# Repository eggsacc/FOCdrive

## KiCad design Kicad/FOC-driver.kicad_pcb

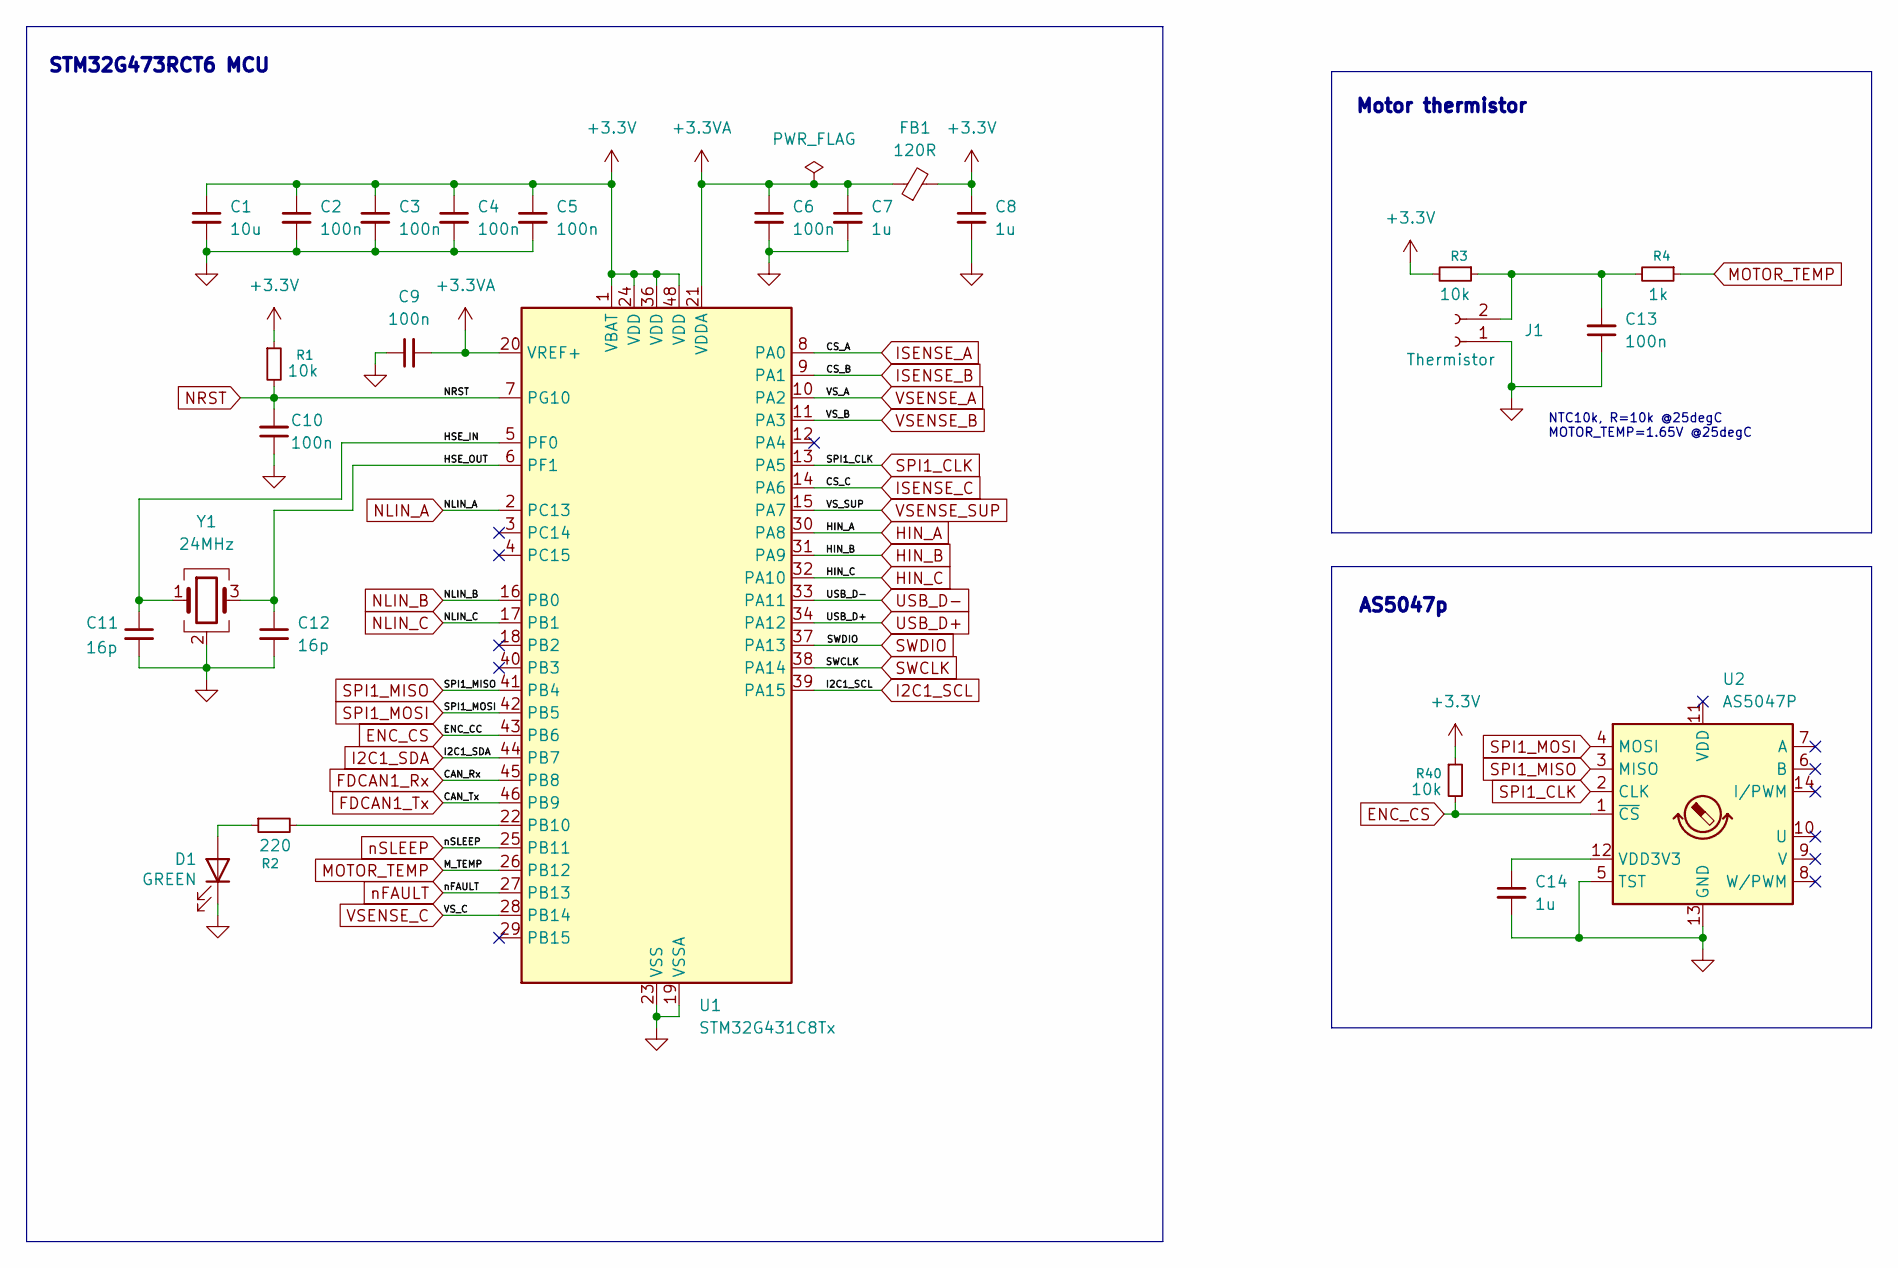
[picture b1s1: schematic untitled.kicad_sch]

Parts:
C1: 10u; C_1206_3216Metric
C2, C3, C4, C5, C6, C9, C13: 100n; C_0402_1005Metric
C7, C8, C14: 1u; C_0603_1608Metric
C10: 100n; C_01005_0402Metric
C11, C12: 16p; C_0402_1005Metric
D1: GREEN; LED_0603_1608Metric
FB1: 120R; L_0603_1608Metric
J1: Thermistor; 2p SolderWire Pad
R1, R3, R40: 10k; R_0402_1005Metric
R2: 220; R_0603_1608Metric
R4: 1k; R_0402_1005Metric
U1: STM32G431C8Tx; LQFP-48_7x7mm_P0.5mm
U2: AS5047P; TSSOP-14_4.4x5mm_P0.65mm
Y1: 24MHz; Crystal_SMD_3225-4Pin_3.2x2.5mm

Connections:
+3.3V: C1.1, C2.1, C3.1, C4.1, C5.1, C8.1, FB1.2, R1.1, R3.2, R40.1, U1.1 (VBAT), U1.24 (VDD), U1.36 (VDD), U1.48 (VDD); also elsewhere on the board
+3.3VA: C6.1, C7.1, C9.2, FB1.1, U1.20 (VREF+), U1.21 (VDDA); also elsewhere on the board
/mcu/HSE_IN: C11.1, U1.5 (PF0), Y1.1
/mcu/HSE_OUT: C12.1, U1.6 (PF1), Y1.3
ENC_CS: R40.2, U1.43 (PB6), U2.1 (~CS)
FDCAN1_Rx: U1.45 (PB8); also elsewhere on the board
FDCAN1_Tx: U1.46 (PB9); also elsewhere on the board
HIN_A: U1.30 (PA8); also elsewhere on the board
HIN_B: U1.31 (PA9); also elsewhere on the board
HIN_C: U1.32 (PA10); also elsewhere on the board
I2C1_SCL: U1.39 (PA15); also elsewhere on the board
I2C1_SDA: U1.44 (PB7); also elsewhere on the board
ISENSE_A: U1.8 (PA0); also elsewhere on the board
ISENSE_B: U1.9 (PA1); also elsewhere on the board
ISENSE_C: U1.14 (PA6); also elsewhere on the board
LSS: C1.2, C2.2, C3.2, C4.2, C5.2, C6.2, C7.2, C8.2, C9.1, C10.1, C11.2, C12.2, C13.1, C14.2, D1.1 (K), J1.1, U1.19 (VSSA), U1.23 (VSS), U1.35 (VSS), U1.47 (VSS), U2.5 (TST), U2.13 (GND), Y1.2 (G), Y1.4 (G); also elsewhere on the board
MOTOR_TEMP: R4.1, U1.26 (PB12)
NLIN_A: U1.2 (PC13); also elsewhere on the board
NLIN_B: U1.16 (PB0); also elsewhere on the board
NLIN_C: U1.17 (PB1); also elsewhere on the board
NRST: C10.2, R1.2, U1.7 (PG10); also elsewhere on the board
unnamed: D1.2 (A), R2.1
unnamed: C13.2, J1.2, R3.1, R4.2
unnamed: R2.2, U1.22 (PB10)
unnamed: C14.1, U2.12 (VDD3V3)
SPI1_CLK: U1.13 (PA5), U2.2 (CLK)
SPI1_MISO: U1.41 (PB4), U2.3 (MISO)
SPI1_MOSI: U1.42 (PB5), U2.4 (MOSI)
SWCLK: U1.38 (PA14); also elsewhere on the board
SWDIO: U1.37 (PA13); also elsewhere on the board
USB_D+: U1.34 (PA12); also elsewhere on the board
USB_D-: U1.33 (PA11); also elsewhere on the board
VSENSE_A: U1.10 (PA2); also elsewhere on the board
VSENSE_B: U1.11 (PA3); also elsewhere on the board
VSENSE_C: U1.28 (PB14); also elsewhere on the board
VSENSE_SUP: U1.15 (PA7); also elsewhere on the board
nFAULT: U1.27 (PB13); also elsewhere on the board
nSLEEP: U1.25 (PB11); also elsewhere on the board

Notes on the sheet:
AS5047p
STM32G473RCT6 MCU
NTC10k, R=10k @25degC MOTOR_TEMP=1.65V @25degC
Motor thermistor

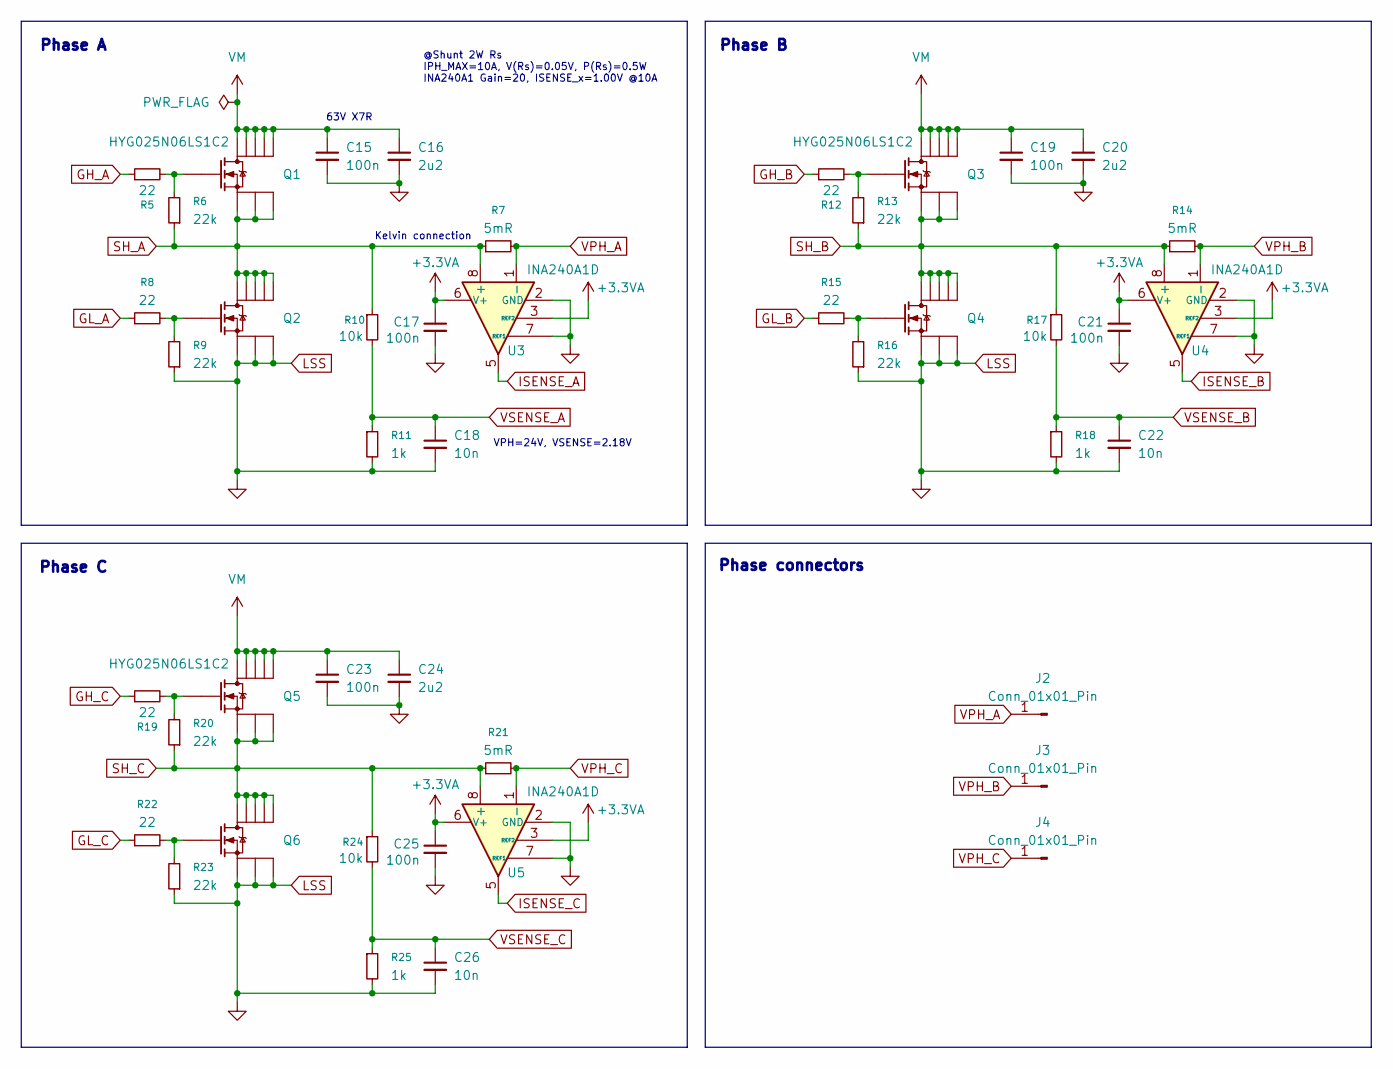
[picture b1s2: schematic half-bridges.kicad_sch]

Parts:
C15, C17, C19, C21, C23, C25: 100n; C_0603_1608Metric
C16, C20, C24: 2u2; C_1206_3216Metric
C18, C22, C26: 10n; C_0402_1005Metric
J2, J3, J4: Conn_01x01_Pin; WireSolder-ID1.6mm-OD3mm
Q1, Q2, Q3, Q4, Q5, Q6: HYG025N06LS1C2
R5, R8, R12, R15, R19, R22: 22; R_0603_1608Metric
R6, R9, R13, R16, R20, R23: 22k; R_0603_1608Metric
R7, R14, R21: 5mR; R_2512_6332Metric
R10, R17, R24: 10k; R_0402_1005Metric
R11, R18, R25: 1k; R_0402_1005Metric
U3, U4, U5: INA240A1D; SOIC-8_3.9x4.9mm_P1.27mm

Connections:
+3.3VA: C17.1, C21.1, C25.1, U3.3 (REF2), U3.6 (V+), U4.3 (REF2), U4.6 (V+), U5.3 (REF2), U5.6 (V+); also elsewhere on the board
GH_A: R5.1; also elsewhere on the board
GH_B: R12.1; also elsewhere on the board
GH_C: R19.1; also elsewhere on the board
GL_A: R8.1; also elsewhere on the board
GL_B: R15.1; also elsewhere on the board
GL_C: R22.1; also elsewhere on the board
ISENSE_A: U3.5; also elsewhere on the board
ISENSE_B: U4.5; also elsewhere on the board
ISENSE_C: U5.5; also elsewhere on the board
LSS: C15.2, C16.2, C17.2, C18.2, C19.2, C20.2, C21.2, C22.2, C23.2, C24.2, C25.2, C26.2, Q2.1 (S), Q2.2 (S), Q2.3 (S), Q4.1 (S), Q4.2 (S), Q4.3 (S), Q6.1 (S), Q6.2 (S), Q6.3 (S), R9.1, R11.2, R16.1, R18.2, R23.1, R25.2, U3.2 (GND), U3.4 (GND), U3.7 (REF1), U4.2 (GND), U4.4 (GND), U4.7 (REF1), U5.2 (GND), U5.4 (GND), U5.7 (REF1); also elsewhere on the board
unnamed: Q1.4 (G), R5.2, R6.2
unnamed: Q2.4 (G), R8.2, R9.2
unnamed: Q3.4 (G), R12.2, R13.2
unnamed: Q4.4 (G), R15.2, R16.2
unnamed: Q5.4 (G), R19.2, R20.2
unnamed: Q6.4 (G), R22.2, R23.2
PVDD: C15.1, C16.1, C19.1, C20.1, C23.1, C24.1, Q1.5 (D), Q1.6, Q1.7, Q1.8, Q1.9, Q3.5 (D), Q3.6, Q3.7, Q3.8, Q3.9, Q5.5 (D), Q5.6, Q5.7, Q5.8, Q5.9; also elsewhere on the board
SH_A: Q1.1 (S), Q1.2 (S), Q1.3 (S), Q2.5 (D), Q2.6, Q2.7, Q2.8, Q2.9, R6.1, R7.1, R10.1, U3.8 (+); also elsewhere on the board
SH_B: Q3.1 (S), Q3.2 (S), Q3.3 (S), Q4.5 (D), Q4.6, Q4.7, Q4.8, Q4.9, R13.1, R14.1, R17.1, U4.8 (+); also elsewhere on the board
SH_C: Q5.1 (S), Q5.2 (S), Q5.3 (S), Q6.5 (D), Q6.6, Q6.7, Q6.8, Q6.9, R20.1, R21.1, R24.1, U5.8 (+); also elsewhere on the board
VPH_A: J2.1 (Pin_1_1), R7.2, U3.1 (-)
VPH_B: J3.1 (Pin_1_1), R14.2, U4.1 (-)
VPH_C: J4.1 (Pin_1_1), R21.2, U5.1 (-)
VSENSE_A: C18.1, R10.2, R11.1; also elsewhere on the board
VSENSE_B: C22.1, R17.2, R18.1; also elsewhere on the board
VSENSE_C: C26.1, R24.2, R25.1; also elsewhere on the board

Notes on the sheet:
Phase A
VPH=24V, VSENSE=2.18V
@Shunt 2W Rs IPH_MAX=10A, V(Rs)=0.05V, P(Rs)=0.5W INA240A1 Gain=20, ISENSE_x=1.00V @10A
Phase B
63V X7R
Phase connectors
Phase C
Kelvin connection

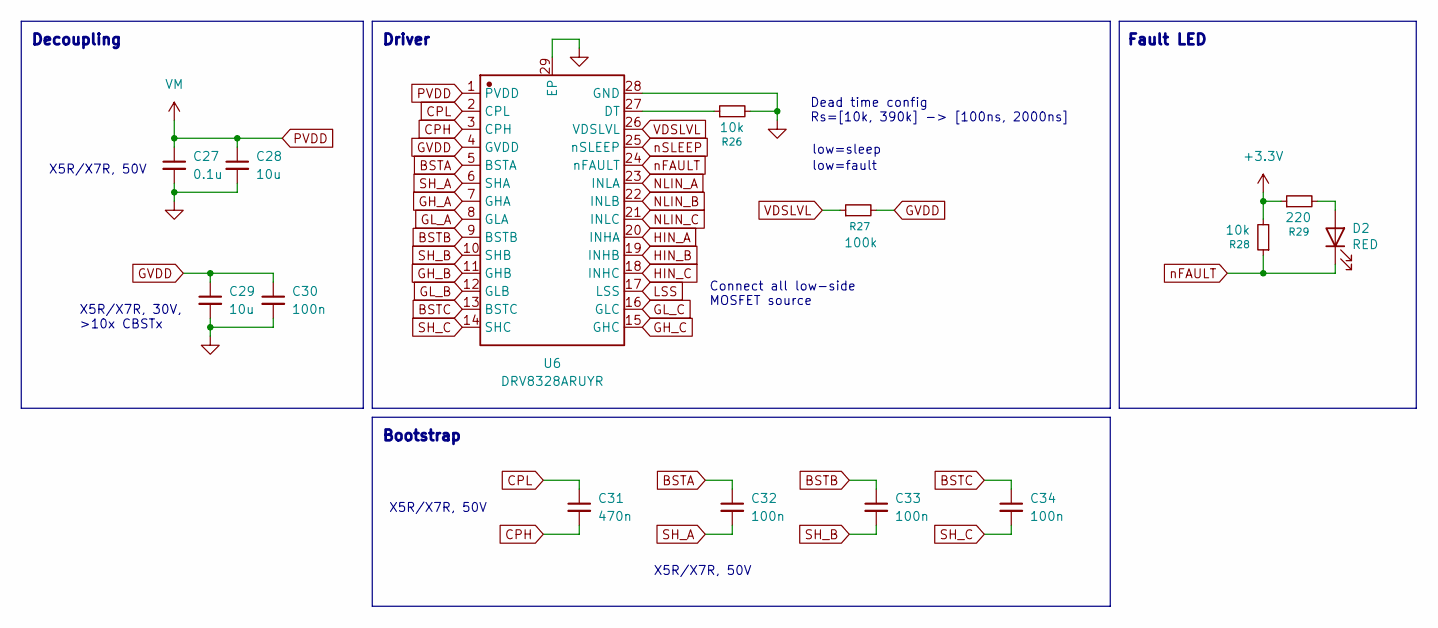
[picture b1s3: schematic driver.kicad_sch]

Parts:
C27: 0.1u; C_0603_1608Metric
C28, C29: 10u; C_1206_3216Metric
C30: 100n; C_0402_1005Metric
C31: 470n; C_0805_2012Metric
C32, C33, C34: 100n; C_0805_2012Metric
D2: RED; LED_0603_1608Metric
R26, R28: 10k; R_0402_1005Metric
R27: 100k; R_0402_1005Metric
R29: 220; R_0603_1608Metric
U6: DRV8328ARUYR; QFN-28_L4.0-W4.0-P0.40-BL-EP2.6 DRV8328; Manufacturer Part DRV8328BRUYR

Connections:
+3.3V: R28.2, R29.1; also elsewhere on the board
BSTA: C32.1, U6.5 (BSTA)
BSTB: C33.1, U6.9 (BSTB)
BSTC: C34.1, U6.13 (BSTC)
CPH: C31.2, U6.3 (CPH)
CPL: C31.1, U6.2 (CPL)
GH_A: U6.7 (GHA); also elsewhere on the board
GH_B: U6.11 (GHB); also elsewhere on the board
GH_C: U6.15 (GHC); also elsewhere on the board
GL_A: U6.8 (GLA); also elsewhere on the board
GL_B: U6.12 (GLB); also elsewhere on the board
GL_C: U6.16 (GLC); also elsewhere on the board
GVDD: C29.1, C30.1, R27.2, U6.4 (GVDD)
HIN_A: U6.20 (INHA); also elsewhere on the board
HIN_B: U6.19 (INHB); also elsewhere on the board
HIN_C: U6.18 (INHC); also elsewhere on the board
LSS: C27.2, C28.2, C29.2, C30.2, R26.2, U6.17 (LSS), U6.28 (GND), U6.29 (EP); also elsewhere on the board
NLIN_A: U6.23 (INLA); also elsewhere on the board
NLIN_B: U6.22 (INLB); also elsewhere on the board
NLIN_C: U6.21 (INLC); also elsewhere on the board
unnamed: D2.2 (A), R29.2
unnamed: R26.1, U6.27 (DT)
PVDD: C27.1, C28.1, U6.1 (PVDD); also elsewhere on the board
SH_A: C32.2, U6.6 (SHA); also elsewhere on the board
SH_B: C33.2, U6.10 (SHB); also elsewhere on the board
SH_C: C34.2, U6.14 (SHC); also elsewhere on the board
VDSLVL: R27.1, U6.26 (VDSLVL)
nFAULT: D2.1 (K), R28.1, U6.24 (nFAULT); also elsewhere on the board
nSLEEP: U6.25 (nSLEEP); also elsewhere on the board

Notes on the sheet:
Bootstrap
Fault LED
Connect all low-side MOSFET source
Driver
X5R/X7R, 50V
Decoupling
low=sleep
low=fault
X5R/X7R, 30V, >10x CBSTx
Dead time config Rs=[10k, 390k] -> [100ns, 2000ns]

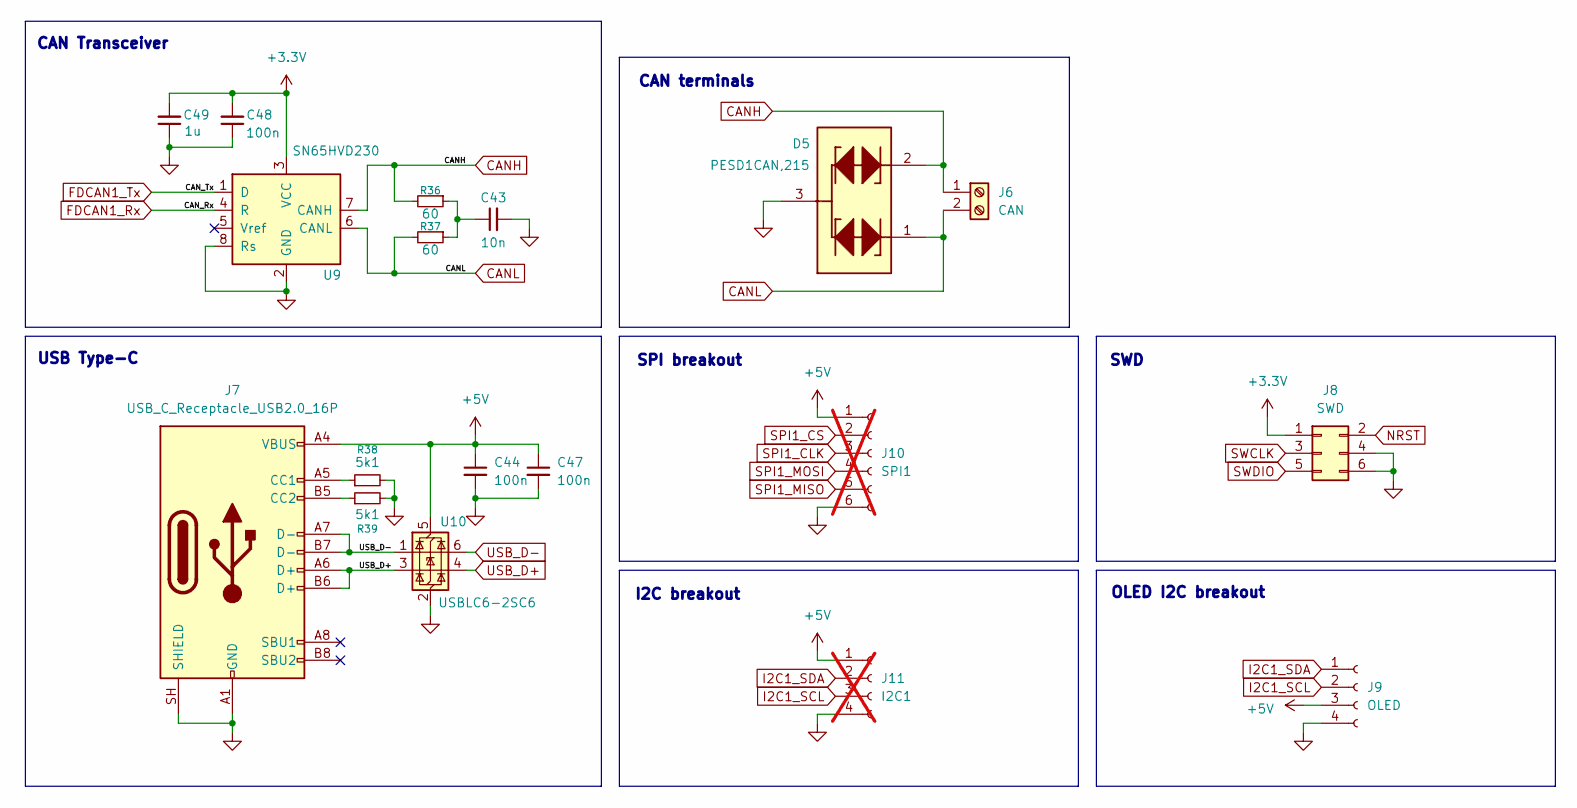
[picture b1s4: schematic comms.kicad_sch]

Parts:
C43: 10n; C_0402_1005Metric
C44, C47, C48: 100n; C_0402_1005Metric
C49: 1u; C_0402_1005Metric
D5: PESD1CAN,215; PESD1CAN; Manufacturer Part PESD1CAN,215
J6: CAN; TerminalBlock_Xinya_XY308-2.54-2P_1x02_P2.54mm_Horizontal
J7: USB_C_Receptacle_USB2.0_16P; USB_C_Receptacle_GCT_USB4105-xx-A_16P_TopMnt_Horizontal
J8: SWD; PinSocket_2x03_P1.27mm_Vertical
J9: OLED; PinSocket_1x04_P2.54mm_Vertical
J10: SPI1; JST_ZE_S06B-ZESK-2D_1x06_P1.50mm_Horizontal; not fitted
J11: I2C1; JST_ZE_S04B-ZESK-2D_1x04_P1.50mm_Horizontal; not fitted
R36, R37: 60; R_0603_1608Metric
R38, R39: 5k1; R_0402_1005Metric
U9: SN65HVD230; SOIC-8_3.9x4.9mm_P1.27mm
U10: USBLC6-2SC6; SOT-23-6

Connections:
+3.3V: C48.2, C49.2, J8.1, U9.3 (VCC); also elsewhere on the board
+5V: C44.1, C47.1, J7.A4 (VBUS), J7.A9 (VBUS), J7.B4 (VBUS), J7.B9 (VBUS), J9.3, J10.1, J11.1, U10.5 (VBUS); also elsewhere on the board
CANH: D5.2, J6.1, R36.2, U9.7 (CANH)
CANL: D5.1, J6.2, R37.2, U9.6 (CANL)
FDCAN1_Rx: U9.4 (R); also elsewhere on the board
FDCAN1_Tx: U9.1 (D); also elsewhere on the board
I2C1_SCL: J9.2, J11.3; also elsewhere on the board
I2C1_SDA: J9.1, J11.2; also elsewhere on the board
LSS: C43.2, C44.2, C47.2, C48.1, C49.1, D5.3, J7.A1 (GND), J7.A12 (GND), J7.B1 (GND), J7.B12 (GND), J7.SH (SHIELD), J8.4, J8.6, J9.4, J10.6, J11.4, R38.2, R39.2, U9.2 (GND), U9.8 (Rs), U10.2 (GND); also elsewhere on the board
NRST: J8.2; also elsewhere on the board
unnamed: C43.1, R36.1, R37.1
unnamed: J7.A5 (CC1), R38.1
unnamed: J7.B5 (CC2), R39.1
SWCLK: J8.3; also elsewhere on the board
SWDIO: J8.5; also elsewhere on the board
USB_D+: J7.A6 (D+), J7.B6 (D+), U10.3 (I/O2), U10.4 (I/O2); also elsewhere on the board
USB_D-: J7.A7 (D-), J7.B7 (D-), U10.1 (I/O1), U10.6 (I/O1); also elsewhere on the board

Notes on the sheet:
OLED I2C breakout
SWD
CAN Transceiver
USB Type-C
SPI breakout
I2C breakout
CAN terminals

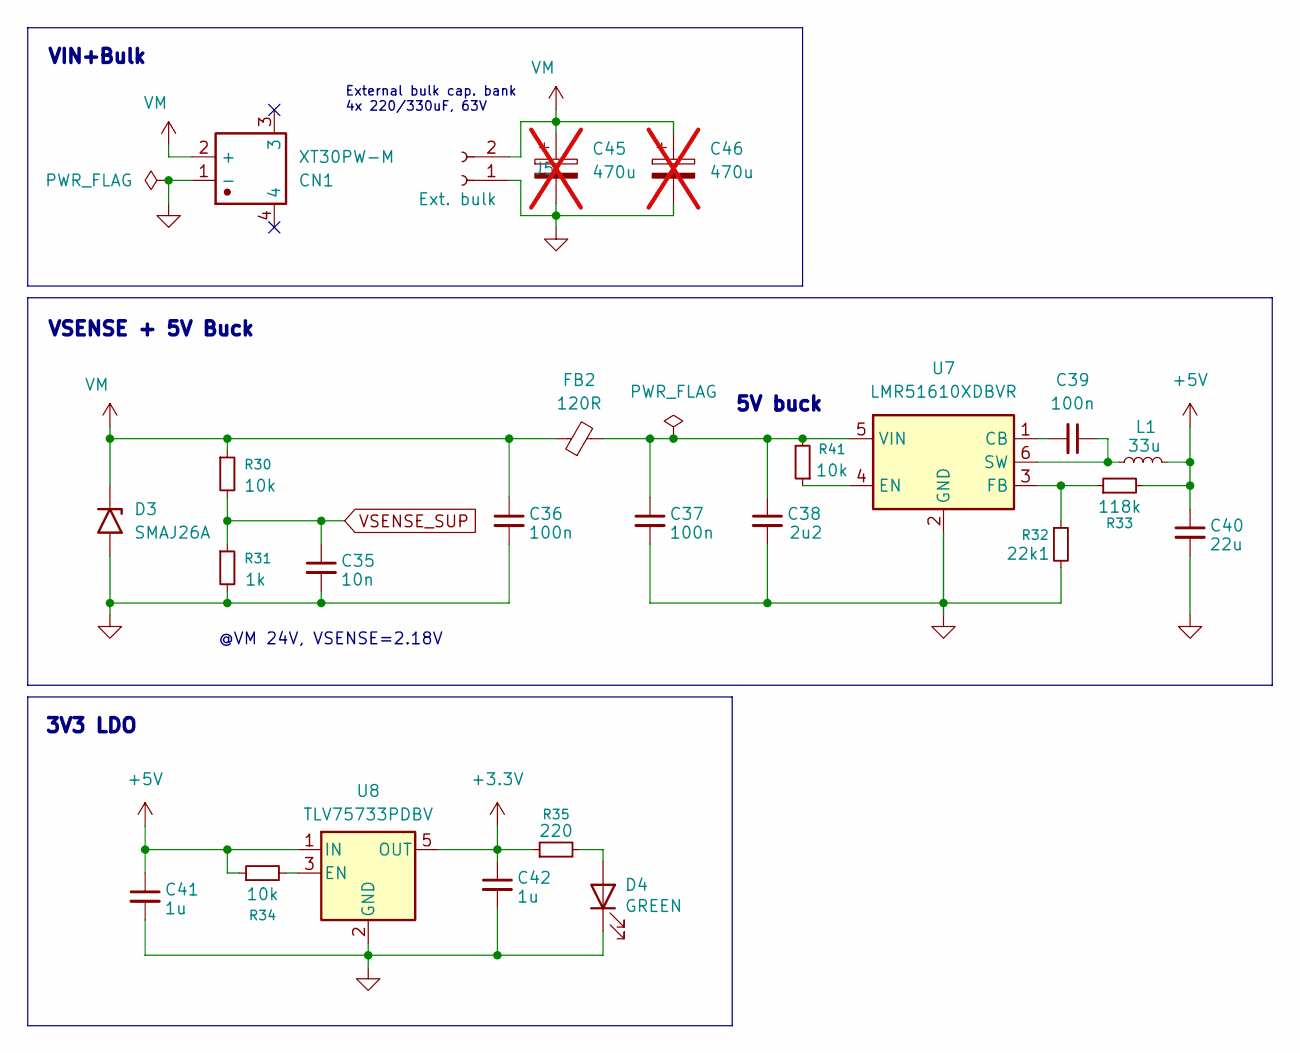
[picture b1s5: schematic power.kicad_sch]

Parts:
C35: 10n; C_0402_1005Metric
C36, C37, C39: 100n; C_0402_1005Metric
C38: 2u2; C_0805_2012Metric
C40: 22u; C_1206_3216Metric
C41, C42: 1u; C_0603_1608Metric
C45, C46: 470u; CP_Elec_10x12.5; not fitted
CN1: XT30PW-M; CONN-TH_XT30PW-M; Manufacturer Part XT60PW-M
D3: SMAJ26A; D_SMA
D4: GREEN; LED_0603_1608Metric
FB2: 120R; L_0603_1608Metric
J5: Ext. bulk; 2p WireSolder 1.3mmID_2mmOD
L1: 33u; L_10.4x10.4_H4.8
R30, R34, R41: 10k; R_0402_1005Metric
R31: 1k; R_0402_1005Metric
R32: 22k1; R_0402_1005Metric
R33: 118k; R_0402_1005Metric
R35: 220; R_0603_1608Metric
U7: LMR51610XDBVR; SOT-23-6
U8: TLV75733PDBV; SOT-23-5

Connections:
+3.3V: C42.1, R35.1, U8.5 (OUT); also elsewhere on the board
+5V: C40.1, C41.1, L1.2, R33.2, R34.1, U8.1 (IN); also elsewhere on the board
LSS: C35.2, C36.2, C37.2, C38.2, C40.2, C41.2, C42.2, C45.2, C46.2, CN1.1 (-), D3.2 (A2), D4.1 (K), J5.1, R31.2, R32.2, U7.2 (GND), U8.2 (GND); also elsewhere on the board
unnamed: D4.2 (A), R35.2
unnamed: C39.2, U7.1 (CB)
unnamed: R41.1, U7.4 (EN)
unnamed: R32.1, R33.1, U7.3 (FB)
unnamed: C39.1, L1.1, U7.6 (SW)
unnamed: C37.1, C38.1, FB2.2, R41.2, U7.5 (VIN)
unnamed: R34.2, U8.3 (EN)
PVDD: C36.1, C45.1, C46.1, CN1.2 (+), D3.1 (A1), FB2.1, J5.2, R30.1; also elsewhere on the board
VSENSE_SUP: C35.1, R30.2, R31.1; also elsewhere on the board

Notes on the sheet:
External bulk cap. bank 4x 220/330uF, 63V
VIN+Bulk
@VM 24V, VSENSE=2.18V
5V buck
3V3 LDO
VSENSE + 5V Buck

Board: 4 copper layers, 123 parts (6 on the bottom side), 79 nets, no tracks yet.

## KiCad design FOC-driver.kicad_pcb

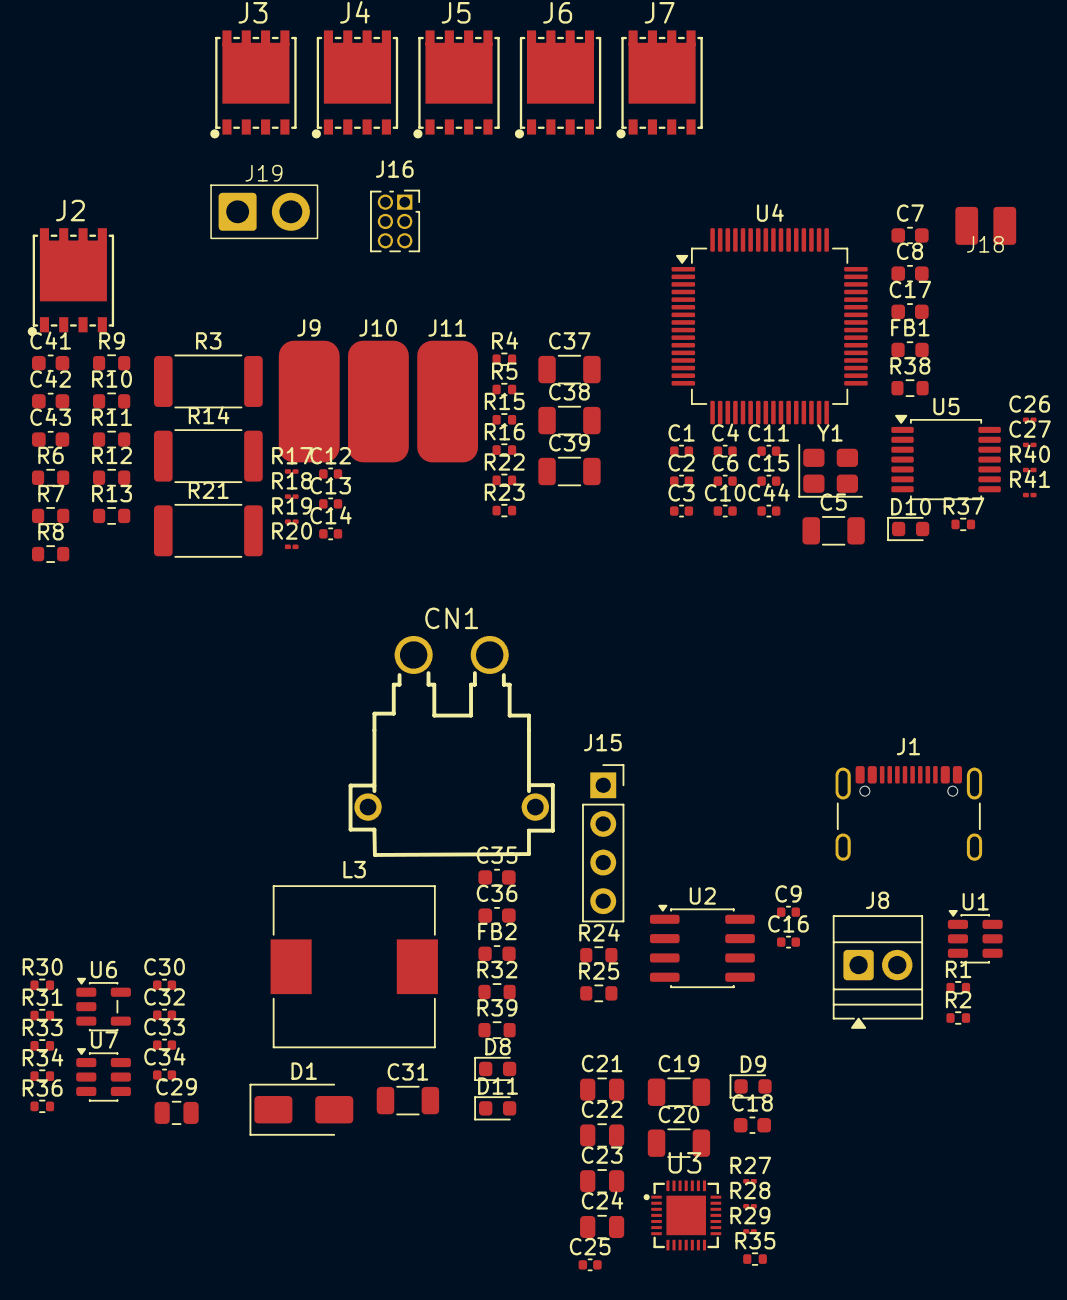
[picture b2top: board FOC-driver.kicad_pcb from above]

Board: 4 copper layers, 114 parts (0 on the bottom side), 76 nets, no tracks yet.

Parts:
C1, C2, C3, C4, C6, C9, C15, C25, C32, C34, C44: 100n; C_0402_1005Metric
C5, C19, C20: 10u; C_1206_3216Metric
C7, C8, C17, C35, C36: 1u; C_0603_1608Metric
C10, C11: 16p; C_0402_1005Metric
C12, C13, C14, C16, C33: 10n; C_0402_1005Metric
C18: 0.1u; C_0603_1608Metric
C21: 470n; C_0805_2012Metric
C22, C23, C24: 100n; C_0805_2012Metric
C26, C27: 100n; C_01005_0402Metric
C29: 2u2; C_0805_2012Metric
C30: 0.1u; C_0402_1005Metric
C31: 22u; C_1206_3216Metric
C37, C38, C39: 2u2; C_1206_3216Metric
C41, C42, C43: 100n; C_0603_1608Metric
CN1: XT30PW-M; CONN-TH_XT30PW-M
D1: SMAJ26A; D_SMA
D8, D10, D11: GREEN; LED_0603_1608Metric
D9: RED; LED_0603_1608Metric
FB1, FB2: 120R; L_0603_1608Metric
J1: USB_C_Receptacle_USB2.0_16P; USB_C_Receptacle_GCT_USB4105-xx-A_16P_TopMnt_Horizontal
J2, J3, J4, J5, J6, J7: HYG025N06LS1C2
J8: CAN; TerminalBlock_Xinya_XY308-2.54-2P_1x02_P2.54mm_Horizontal
J9, J10, J11: Conn_01x01_Pin; SolderWirePad_1x01_SMD_4x8mm
J15: OLED; PinSocket_1x04_P2.54mm_Vertical
J16: SWD; PinSocket_2x03_P1.27mm_Vertical
J18: Thermistor; 2p SolderWire Pad
J19: Ext. bulk; 2p WireSolder 1.5mmID_2.5mmOD
L3: 33u; L_10.4x10.4_H4.8
R1, R2: 5k1; R_0402_1005Metric
R3, R14, R21: 1mR; R_2512_6332Metric
R4, R16, R23, R34: 1k; R_0402_1005Metric
R5, R15, R22, R33, R36, R37: 10k; R_0402_1005Metric
R6, R7, R10, R11: 22; R_0603_1608Metric
R8, R9, R12, R13: 22k; R_0603_1608Metric
R17, R18: 22; R_01005_0402Metric
R19, R20: 22k; R_01005_0402Metric
R24, R25: 60; R_0603_1608Metric
R27, R29, R40: 10k; R_01005_0402Metric
R28: 220; R_01005_0402Metric
R30: 22k1; R_0402_1005Metric
R31: 118k; R_0402_1005Metric
R32: 330; R_0603_1608Metric
R35: 100k; R_0402_1005Metric
R38, R39: 220; R_0603_1608Metric
R41: 1k; R_01005_0402Metric
U1: USBLC6-2SC6; SOT-23-6
U2: SN65HVD230; SOIC-8_3.9x4.9mm_P1.27mm
U3: DRV8328ARUYR; QFN-28_L4.0-W4.0-P0.40-BL-EP2.6 DRV8328
U4: STM32G473RCTx; LQFP-64_10x10mm_P0.5mm
U5: AS5047P; TSSOP-14_4.4x5mm_P0.65mm
U6: TLV75733PDBV; SOT-23-5
U7: LMR51610XDBVR; SOT-23-6
Y1: 24MHz; Crystal_SMD_3225-4Pin_3.2x2.5mm

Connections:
+3.3V: C1.1, C2.1, C3.1, C4.1, C5.1, C7.1, C15.1, C36.1, FB1.2, J16.1, R28.1, R29.2, R39.1, R40.2, U2.3 (VCC), U4.1 (VBAT), U4.16 (VDD), U4.32 (VDD), U4.48 (VDD), U4.64 (VDD), U6.5 (OUT)
+3.3VA: C6.1, C8.1, C26.2, FB1.1, R37.1, U4.28 (VREF+), U4.29 (VDDA)
+5V: C9.1, C31.1, C35.1, J1.A4 (VBUS), J1.A9 (VBUS), J1.B4 (VBUS), J1.B9 (VBUS), J15.3, L3.2, R31.2, R32.1, R36.1, U1.5 (VBUS), U5.11 (VDD), U6.1 (IN)
BSTA: C22.1, U3.5 (BSTA)
BSTB: C23.1, U3.9 (BSTB)
BSTC: C24.1, U3.13 (BSTC)
CANH: J8.1, R24.2, U2.7 (CANH)
CANL: J8.2, R25.2, U2.6 (CANL)
CPH: C21.2, U3.3 (CPH)
CPL: C21.1, U3.2 (CPL)
ENC_CS: U4.18 (PA4), U5.1 (~CS)
FDCAN1_Rx: U2.4 (R), U4.61 (PB8)
FDCAN1_Tx: U2.1 (D), U4.62 (PB9)
GH_A: R6.1, U3.7 (GHA)
GH_B: R10.1, U3.11 (GHB)
GH_C: R17.1, U3.15 (GHC)
GL_A: R7.1, U3.8 (GLA)
GL_B: R11.1, U3.12 (GLB)
GL_C: R18.1, U3.16 (GLC)
GND: C1.2, C2.2, C3.2, C4.2, C5.2, C6.2, C7.2, C8.2, C9.2, C10.2, C11.2, C12.2, C13.2, C14.2, C15.2, C16.2, C17.2, C18.2, C19.2, C20.2, C25.2, C26.1, C27.1, C29.2, C31.2, C32.2, C33.2, C34.2, C35.2, C36.2, C37.2, C38.2, C39.2, C41.2, C42.2, C43.2, C44.1, CN1.1 (-), D1.2 (A2), D8.1 (K), D10.1 (K), D11.1 (K), J1.A1 (GND), J1.A12 (GND), J1.B1 (GND), J1.B12 (GND), J1.SH (SHIELD), J15.4, J16.4, J16.6, J18.1, J19.1, R1.2, R2.2, R3.2, R4.2, R14.2, R16.2, R21.2, R23.2, R27.2, R30.2, R34.2, U1.2 (GND), U2.2 (GND), U2.8 (Rs), U3.28 (GND), U3.29 (EP), U4.15 (VSS), U4.27 (VSSA), U4.31 (VSS), U4.47 (VSS), U4.63 (VSS), U5.5 (TST), U5.13 (GND), U6.2 (GND), U7.1 (GND), Y1.2 (G), Y1.4 (G)
GVDD: C20.1, C25.1, R35.2, U3.4 (GVDD)
HIN_A: U3.20 (INHA), U4.42 (PA8)
HIN_B: U3.19 (INHB), U4.9 (PC1)
HIN_C: U3.18 (INHC), U4.10 (PC2)
I2C1_SCL: J15.2, U4.51 (PA15)
I2C1_SDA: J15.1, U4.60 (PB7)
ISENSE_A: J3.1 (S), J3.2 (S), J3.3 (S), J5.1 (S), J5.2 (S), J5.3 (S), J7.1 (S), J7.2 (S), J7.3 (S), R3.1, R9.1, R13.1, R14.1, R20.1, R21.1, U3.17 (LSS), U4.21 (PA7), U4.35 (PB13), U4.36 (PB14)
MOTOR_TEMP: R41.1, U4.8 (PC0)
NLIN_A: U3.23 (INLA), U4.2 (PC13)
NLIN_B: U3.22 (INLB), U4.24 (PB0)
NLIN_C: U3.21 (INLC), U4.25 (PB1)
NRST: C27.2, J16.2, R37.2, U4.7 (PG10)
unnamed: C16.1, R24.1, R25.1
unnamed: D8.2 (A), R32.2
unnamed: D9.2 (A), R28.2
unnamed: D10.2 (A), R38.1
unnamed: D11.2 (A), R39.2
unnamed: J1.A5 (CC1), R1.1
unnamed: J1.B5 (CC2), R2.1
unnamed: J1.A6 (D+), J1.B6 (D+), U1.3 (I/O2)
unnamed: J1.A7 (D-), J1.B7 (D-), U1.1 (I/O1)
unnamed: J2.4 (G), R6.2, R8.2
unnamed: J3.4 (G), R7.2, R9.2
unnamed: J4.4 (G), R17.2, R19.2
unnamed: J5.4 (G), R18.2, R20.2
unnamed: J6.4 (G_4), R10.2, R12.2
unnamed: J7.4 (G), R11.2, R13.2
unnamed: C44.2, J18.2, R40.1, R41.2
unnamed: R27.1, U3.27 (DT)
unnamed: R38.2, U4.26 (PB2)
unnamed: C10.1, U4.5 (PF0), Y1.1
unnamed: C11.1, U4.6 (PF1), Y1.3
unnamed: C17.1, U5.12 (VDD3V3)
unnamed: R36.2, U6.3 (EN)
unnamed: C30.2, U7.6 (CB)
unnamed: C29.1, C34.1, FB2.2, U7.3 (VIN), U7.5 (EN)
unnamed: R30.1, R31.1, U7.4 (FB)
unnamed: C30.1, L3.1, U7.2 (SW)
PVDD: C18.1, C19.1, C32.1, C37.1, C38.1, C39.1, C41.1, C42.1, C43.1, CN1.2 (+), D1.1 (A1), FB2.1, J2.5 (D), J2.6, J2.7, J2.8, J2.9, J4.5 (D), J4.6, J4.7, J4.8, J4.9, J19.2, R33.1, U3.1 (PVDD)
SH_A: C22.2, J2.1 (S), J2.2 (S), J2.3 (S), J3.5 (D), J3.6, J3.7, J3.8, J3.9, J9.1 (Pin_1_1), R5.1, R8.1, U3.6 (SHA)
SH_B: C23.2, J7.5 (D), J7.6, J7.7, J7.8, J7.9, J10.1 (Pin_1_1), R12.1, R15.1, U3.10 (SHB)
SH_C: C24.2, J4.1 (S), J4.2 (S), J4.3 (S), J5.5 (D), J5.6, J5.7, J5.8, J5.9, J11.1 (Pin_1_1), R19.1, R22.1, U3.14 (SHC)
SPI1_CLK: U4.19 (PA5), U5.2 (CLK)
SPI1_MISO: U4.20 (PA6), U5.3 (MISO)
SPI1_MOSI: U4.58 (PB5), U5.4 (MOSI)
SWCLK: J16.3, U4.50 (PA14)
SWDIO: J16.5, U4.49 (PA13)
USB_D+: U1.4 (I/O2), U4.46 (PA12)
USB_D-: U1.6 (I/O1), U4.45 (PA11)
VDSLVL: R35.1, U3.26 (VDSLVL)
VSENSE_A: C12.1, R4.1, R5.2, U4.12 (PA0)
VSENSE_B: C13.1, R15.2, R16.1, U4.13 (PA1)
VSENSE_C: C14.1, R22.2, R23.1, U4.14 (PA2)
VSENSE_SUP: C33.1, R33.2, R34.1, U4.17 (PA3)
nFAULT: D9.1 (K), R29.1, U3.24 (nFAULT), U4.22 (PC4)
nSLEEP: U3.25 (nSLEEP), U4.23 (PC5)

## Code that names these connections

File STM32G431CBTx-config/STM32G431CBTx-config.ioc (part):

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Mcu.Name=STM32G431C(6-8-B)Tx
Mcu.Package=LQFP48
Mcu.UserName=STM32G431CBTx
PA0.GPIOParameters=GPIO_Label
PA0.GPIO_Label=ISENSE_A
PA0.Mode=IN1-Single-Ended
PA0.Signal=ADC1_IN1
PA1.GPIOParameters=GPIO_Label
PA1.GPIO_Label=ISENSE_B
PA1.Mode=IN2-Single-Ended
PA1.Signal=ADC1_IN2
PA10.Signal=S_TIM1_CH3
PA11.Mode=Device
PA11.Signal=USB_DM
PA12.Mode=Device
PA12.Signal=USB_DP
PA13.Mode=Serial_Wire
PA13.Signal=SYS_JTMS-SWDIO
PA14.Mode=Serial_Wire
PA14.Signal=SYS_JTCK-SWCLK
PA15.Mode=I2C
PA15.Signal=I2C1_SCL
PA2.GPIOParameters=GPIO_Label
PA2.GPIO_Label=VSENSE_A
PA2.Mode=IN3-Single-Ended
PA2.Signal=ADC1_IN3
PA3.GPIOParameters=GPIO_Label
PA3.GPIO_Label=VSENSE_B
PA3.Mode=IN4-Single-Ended
PA3.Signal=ADC1_IN4
PA5.Mode=Full_Duplex_Master
PA5.Signal=SPI1_SCK
PA6.GPIOParameters=GPIO_Label
PA6.GPIO_Label=ISENSE_C
PA6.Mode=IN3-Single-Ended
PA6.Signal=ADC2_IN3
PA7.GPIOParameters=GPIO_Label
PA7.GPIO_Label=VSENSE_SUP
PA7.Mode=IN4-Single-Ended
PA7.Signal=ADC2_IN4
PA8.Signal=S_TIM1_CH1
PA9.Signal=S_TIM1_CH2
PB0.Mode=PWM Generation2 CH2 CH2N
PB0.Signal=TIM1_CH2N
PB1.Mode=PWM Generation3 CH3 CH3N
PB1.Signal=TIM1_CH3N
PB10.GPIOParameters=GPIO_Label
PB10.GPIO_Label=STATUS_LED
PB10.Signal=GPIO_Output
PB11.Signal=GPIO_Output
PB12.GPIOParameters=GPIO_Label
PB12.GPIO_Label=MOTOR_TEMP
PB12.Mode=IN11-Single-Ended
PB12.Signal=ADC1_IN11
PB13.GPIOParameters=GPIO_Label
PB13.GPIO_Label=nFAULT
PB13.Signal=GPIO_Input
PB14.GPIOParameters=GPIO_Label
PB14.GPIO_Label=VSENSE_C
PB14.Mode=IN5-Single-Ended
PB14.Signal=ADC1_IN5
PB4.Mode=Full_Duplex_Master
PB4.Signal=SPI1_MISO
PB5.Mode=Full_Duplex_Master
PB5.Signal=SPI1_MOSI
PB6.GPIOParameters=GPIO_Label
PB6.GPIO_Label=ENC_CS
PB6.Signal=GPIO_Output
PB7.Mode=I2C
PB7.Signal=I2C1_SDA
PB8-BOOT0.Mode=FDCAN_Activate
PB8-BOOT0.Signal=FDCAN1_RX
PB9.Mode=FDCAN_Activate
PB9.Signal=FDCAN1_TX
PC13.Mode=PWM Generation1 CH1 CH1N
PC13.Signal=TIM1_CH1N
PF0-OSC_IN.Mode=HSE-External-Oscillator
PF0-OSC_IN.Signal=RCC_OSC_IN
PF1-OSC_OUT.Mode=HSE-External-Oscillator
PF1-OSC_OUT.Signal=RCC_OSC_OUT
RCC.HSE_VALUE=24000000
RCC.SYSCLKFreq_VALUE=170000000
RCC.SYSCLKSource=RCC_SYSCLKSOURCE_PLLCLK
board=custom

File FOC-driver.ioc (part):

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Mcu.Name=STM32G473R(B-C-E)Tx
Mcu.Package=LQFP64
Mcu.UserName=STM32G473RCTx
PA0.Mode=IN1-Single-Ended
PA0.Signal=ADC2_IN1
PA1.Mode=IN2-Single-Ended
PA1.Signal=ADC1_IN2
PA11.Mode=Device
PA11.Signal=USB_DM
PA12.Mode=Device
PA12.Signal=USB_DP
PA13.Mode=Serial_Wire
PA13.Signal=SYS_JTMS-SWDIO
PA14.Mode=Serial_Wire
PA14.Signal=SYS_JTCK-SWCLK
PA15.Mode=I2C
PA15.Signal=I2C1_SCL
PA2.Mode=IN3-Single-Ended
PA2.Signal=ADC1_IN3
PA3.Mode=IN4-Single-Ended
PA3.Signal=ADC1_IN4
PA4.Signal=GPIO_Output
PA5.Mode=Full_Duplex_Master
PA5.Signal=SPI1_SCK
PA6.Mode=IN3-Single-Ended
PA6.Signal=ADC2_IN3
PA7.Mode=IN4-Single-Ended
PA7.Signal=ADC2_IN4
PA8.Signal=S_TIM1_CH1
PB0.Mode=PWM Generation2 CH2 CH2N
PB0.Signal=TIM1_CH2N
PB1.Mode=PWM Generation3 CH3 CH3N
PB1.Signal=TIM1_CH3N
PB14.Mode=IN5-Single-Ended
PB14.Signal=ADC1_IN5
PB4.Mode=Full_Duplex_Master
PB4.Signal=SPI1_MISO
PB5.Mode=Full_Duplex_Master
PB5.Signal=SPI1_MOSI
PB6.GPIOParameters=GPIO_Label
PB6.GPIO_Label=SPI1_CS
PB6.Signal=GPIO_Output
PB7.Mode=I2C
PB7.Signal=I2C1_SDA
PB8-BOOT0.Mode=FDCAN_Activate
PB8-BOOT0.Signal=FDCAN1_RX
PB9.Mode=FDCAN_Activate
PB9.Signal=FDCAN1_TX
PC0.Mode=IN6-Single-Ended
PC0.Signal=ADC1_IN6
PC1.Signal=S_TIM1_CH2
PC13.Mode=PWM Generation1 CH1 CH1N
PC13.Signal=TIM1_CH1N
PC2.Signal=S_TIM1_CH3
PC4.GPIOParameters=GPIO_Label
PC4.GPIO_Label=nFAULT
PC4.Signal=GPXTI4
PC5.GPIOParameters=GPIO_Label
PC5.GPIO_Label=nSLEEP
PC5.Signal=GPIO_Output
PF0-OSC_IN.Mode=HSE-External-Oscillator
PF0-OSC_IN.Signal=RCC_OSC_IN
PF1-OSC_OUT.Mode=HSE-External-Oscillator
PF1-OSC_OUT.Signal=RCC_OSC_OUT
RCC.HSE_VALUE=24000000
RCC.SYSCLKFreq_VALUE=170000000
RCC.SYSCLKSource=RCC_SYSCLKSOURCE_PLLCLK
board=custom
